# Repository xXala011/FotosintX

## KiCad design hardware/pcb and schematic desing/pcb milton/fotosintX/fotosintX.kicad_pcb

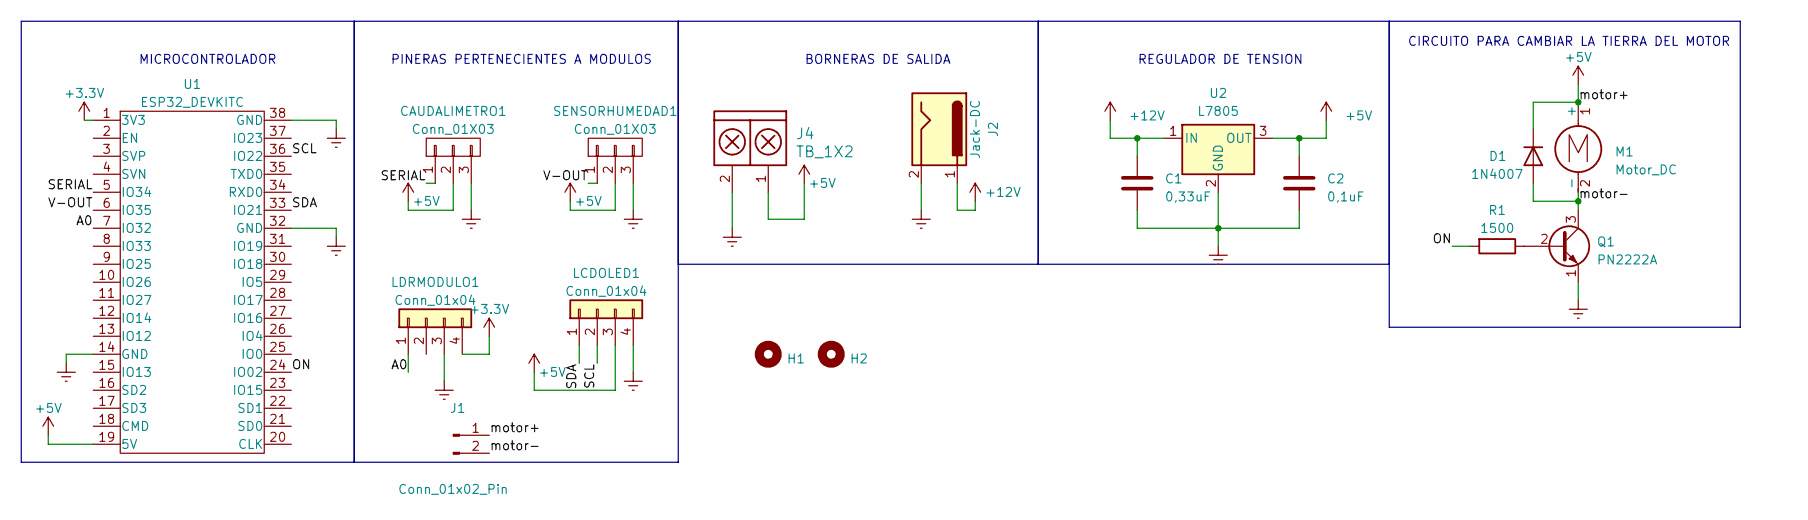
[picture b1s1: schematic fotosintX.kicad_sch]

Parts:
C1: 0,33uF; CAP_0.1
C2: 0,1uF; CAP_0.1
CAUDALIMETRO1: Conn_01X03; Pin_Strip_3
D1: 1N4007; D_DO-41_SOD81_P10.16mm_Horizontal
H1, H2: Mounting_Hole; hole_3mm
J1: Conn_01x02_Pin; PinHeader_1x02_P2.54mm_Vertical
J2: Jack-DC; CUI_PJ-037AH
J4: TB_1X2; BORNERA2
LCDOLED1: Conn_01x04; pin_strip_4
LDRMODULO1: Conn_01x04; pin_strip_4
M1: Motor_DC
Q1: PN2222A; TO-92_Wide
R1: 1500; RES0.3
SENSORHUMEDAD1: Conn_01X03; Pin_Strip_3
U1: ESP32_DEVKITC; ESP32S
U2: L7805; TO-220

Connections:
+3.3V: LDRMODULO1.4, U1.1 (3V3)
+5V: C2.1, CAUDALIMETRO1.2, D1.1 (K), J1.1, J4.1, LCDOLED1.3, M1.1 (+), SENSORHUMEDAD1.2, U1.19 (5V), U2.3 (OUT)
+12V: C1.1, J2.1, U2.1 (IN)
/A0: LDRMODULO1.1, U1.7 (IO32)
/AUOT: SENSORHUMEDAD1.1, U1.6 (IO35)
/ON: R1.2, U1.24 (IO02)
/SCL: LCDOLED1.2, U1.36 (IO22)
/SDA: LCDOLED1.1, U1.33 (IO21)
/SERIAL: CAUDALIMETRO1.1, U1.5 (IO34)
/motor-: D1.2 (A), J1.2, M1.2 (-), Q1.3 (C)
Earth: C1.2, C2.2, CAUDALIMETRO1.3, J2.2, J4.2, LCDOLED1.4, LDRMODULO1.3, Q1.1 (E), SENSORHUMEDAD1.3, U1.14 (GND), U1.32 (GND), U1.38 (GND), U2.2 (GND)
unnamed: Q1.2 (B), R1.1

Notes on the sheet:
REGULADOR DE TENSION
MICROCONTROLADOR
PINERAS PERTENECIENTES A MODULOS
BORNERAS DE SALIDA
CIRCUITO PARA CAMBIAR LA TIERRA DEL MOTOR

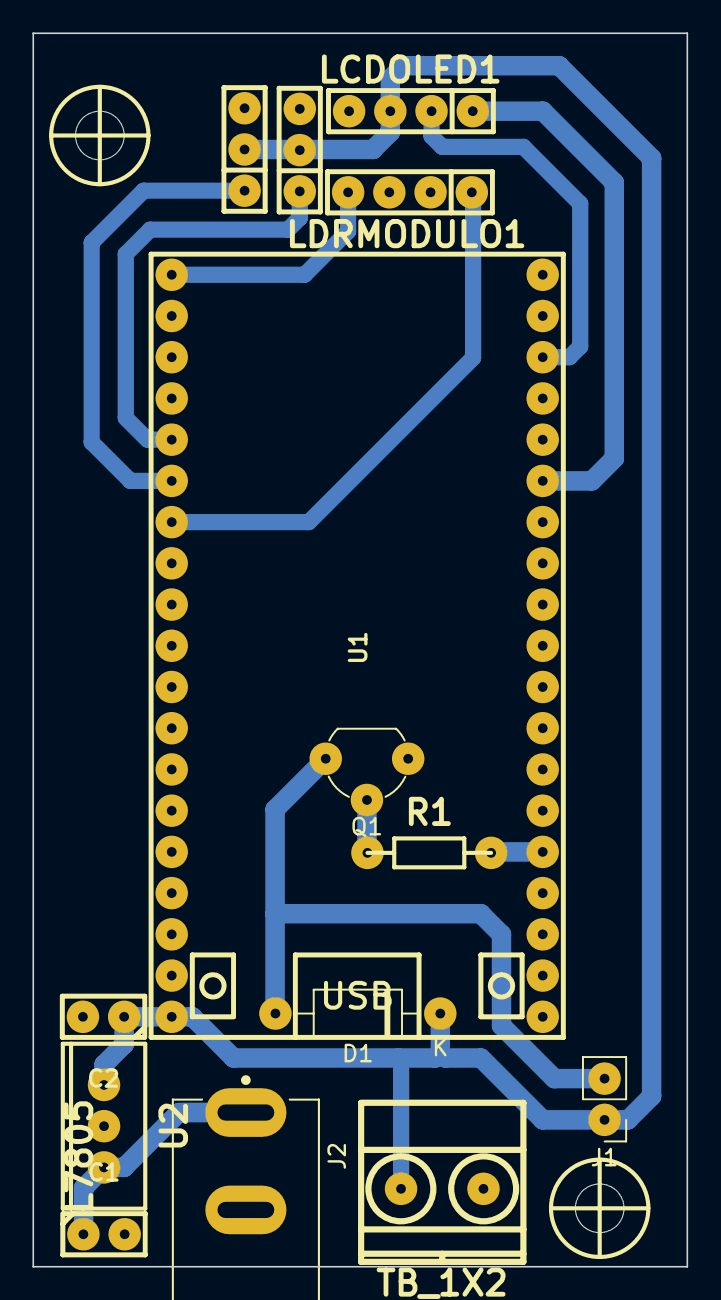
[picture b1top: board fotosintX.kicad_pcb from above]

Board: 2 copper layers, 40.3 x 76.0 mm, 16 parts (1 on the bottom side), 12 nets.

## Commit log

2023-04-10 Se inicia el proyecto
2023-04-10 prueba
2023-04-11 creacion del pcb/milton
2023-04-11 arreglo de carpetas
2023-04-11 añadiendo documentacion
2023-04-11 Mejorando pcb
2023-04-13 Agregue los Modelos 3d V1.1 FotosintX
2023-04-13 bug de mi cerebro perdon
2023-04-19 me olvide de ponerle el valor ala resistencia :V
2023-04-19 arregle el schematic
2023-04-21 pcb modified
2023-04-21 add pcb printing pdf
2023-04-21 edit pcb print pdf
2023-04-21 add schematic print
2023-04-24 PCB terminado
2023-04-28 MQTT, water bump and water flow test
2023-04-28 Correct Errors
2023-04-28 edit utlis.h file
2023-04-29 added WiFiKeys header example
2023-04-29 correct password name variable in header WiFiKeys
2023-04-30 i can use client.publish() in callbackFunc
2023-04-30 callbackFunc() error solved
2023-05-01 resolve some errors
2023-05-01 water pump, water flow and MQTT code made
2023-05-04 last update, with new logic
2023-05-05 arreglando un error
2023-05-05 video documentation about the website
2023-05-08 Correccion final
2023-05-29 subiendo pagina web no terminada
2023-07-14 test kicad-utils lib
